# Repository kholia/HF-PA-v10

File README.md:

Why?

We need a QRP PA which does NOT blow up (unlike those 3xBS170 and 4xBS170
designs). We believe that if the FETs blow up (despite best practices and
intentions but under less-than-ideal external conditions), then the design has
FAILED!

[Inspirational Video Link](https://www.youtube.com/watch?v=4r7wHMg5Yjg)

Update (August-2024): https://github.com/kholia/HF-PA-v10/tree/master/IRFP-Hacks-v5-SMD
(or v4 for THT regulator) and SUPSiC GC2M0280120D is all you need for 30W
All-HF PA for 4 USD. For 30W All-HF PA @ 8.5 USD, my tested MOSFET is CREE
C2M0280120D. Use 7815 regulator for powering the UCC gate driver when using the
`*C2M0280120D` MOSFET. SUPSiC GC3M0280090D works very well too and is our top
choice now (as of September, 2024).

Important update (February-2024): LC match for IRF510 @ 28 MHz. 7 turns FT50-6
and 220pF capacitor. Corrected PAE figure is around 50%. 30v @ drain produces
roughly 10W of clean'ish looking RF output. 24v @ drain produces 6W @ 28 MHz.
17v @ drain produces 3.7W.

March-2024 update: LC match for IRF510 @ 50 MHz. T50-6 4 turns and 180pF
capacitor. 24v @ drain produces clean'ish 28.8 Vpp (~2W). PAE is around 25%.
Such is life...

Update (29-September-2023): By removing the gate resistor, we firmly push the
amplifier into more Class-D operation. The MOSFET now remains as cool as a
cucumber!

Update (10-September-2023): The PCB was successfully validated!

Output is 7 to 8 W (before LPF) over a range of 160m to 10m as expected, with a
15V SMPS power supply. With a Pro-BPF attached, the power output is ~5W even at
28 MHz with IRF510! It even puts out 2W @ 50 MHz!

Amplifier characterization (@ 30.7 MHz for some reason, before LPF):

7 volts -> 2W

8 volts -> 3W

9 volts -> 3.5W

10 volts -> 4W

11 volts -> 5W

12 volts -> 6W

14 volts -> 8W

Efficiency is in the range of 45 to 50% which isn't bad ;)

Another result: 17 volts. 14 MHz. NKK LPF. 17.3W DC in. 57.6 clean Vpp on
scope. 8.3W clean RF output @ 48% efficiency!

BOM cost (minimal version): < 450 INR only - beat this! ;)

Note: HF-PA-v10 is also known as `CoolAMP (TM)`.

Build Notes:

- Use a 15V / 16v power supply.

- If you want to use a 13.8V power supply, then

  - Do NOT install the 78M12 regulator

  - Bridge the JP2 jumper

- Use adequate heatsinking. I use a 100x100x200 aluminium block with a 12v fan
  for doing WSPR activities. The MOSFET temperature stays under 45 degrees this
  way.

- PTT is active high - 3.3v is enough to trigger PTT.

- To skip the PTT sub-circuit, bridge the AOD407 MOSFET's source to drain.

- This amplifier can be directly driven by Si5351 (use 8mA drive setting)!

- IMPORTANT: For safety and RF output control, use a `10A DC-DC Step-down
  Adjustable Constant Voltage Module` or something similar.

  - https://robu.in/product/10a-dc-dc-step-down-adjustable-constant-voltage-module/

Results:

Fun on WSPR:

Note: I am using a 5-meter long EFHW antenna tuned for the 10m band along with
~45 meters of HLF-240 coax. Your results should be better than mine ;)

Quick Hacks:

I am using one v10 board (on low power setting of ~1 to 2W) to drive the second
v10 board.

The second v10 board has IRF530 on it. It uses a simple 3R3 SMD drain choke,
240nH inductor (8 turns on T50-6) + 470 pF LC match for the 20m band at the
output side.

The power output is 20W+ with 30v at the IRF530 drain. While this is fine for
FT8, we decrease the output power to 9 to 12W for WSPR mode (considering
derating, heat dissipation, fear of "flash over")

December-2023 update: We can now use IRFP140N (with its massive TO-247 package)
to generate around "20W" safely for WSPR. We drive the IRFP140N MOSFET directly
with the UCC driver chip now.

Settings: UCC driver at roughly 12v. With LC match set for 20m band (NB!).

IRFP140N @ 28v drain @ 14 MHz -> 22W

IRFP140N @ 28v drain @ 3.5 MHz -> 20W (for Rafal)

IRFP140N @ 28v drain @ 7 MHz -> 20W

We believe we can push 25W easily by feeding 14v to 15v to the UCC driver chip.

The "final" IRFP140N MOSFET remains as cool as a cucumber, pretty boring -
right? Where have the "exciting" days of the MOSFETs blowing up in your face
gone? Just kidding!

NB: To overcome antenna losses (~2.0 SWR 20m dipole), lossy 50m meters of
HLF-200 coax, we need to generate around 15W+ on the amplifier side.

```
In [1]: 15W * 0.88 (SWR losses) * 0.40 (coax losses)
Out[1]: 5.28
```

PA protection:

- We plan to use INA219 to monitor current consumption, and to terminate TX if
  anomalies are detected.

- Use `thermocouple` attached to the MOSFET's body using thermoglue to monitor
  the temperature, and to terminate TX if anomalies are detected.

New discoveries (via https://github.com/rafal-rozestwinski):

- Power output is 1 to 1.5W on 50 MHz.

- The PA survives open and short conditions but protections are recommended in
  any case.

  - INA219 based current monitoring

  - Thermocouple based temperature monitoring

- We do NOT recommend the old-skool SWR monitoring approach due to its
  complexity (for end-users).

Learnings:

- Keep the IRF510's gate voltage <=9 volts.

  If the IRF510's gate voltage is too high (i.e. when IRF510 is over-driven),
  it results in super wide-band distorted noisy signal on the output - you
  don't want that ;)

  If you want to feed high voltages to IRF's drain, then use a regulator (9v)
  for powering the UCC driver chip.

Joining In:

Are you interested in such projects, and spam-free technical discussions?

If yes, you might be interested in joining [the 'HAMBREWERS' Telegram group](https://t.me/+TwzGyKGe8_QI_B3y).

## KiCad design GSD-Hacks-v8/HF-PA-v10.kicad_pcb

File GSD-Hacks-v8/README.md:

This version uses a GaN gate driver (MX1025D) and GSD pinout TO-252 package GaN FET. It also uses a cost-effective Chinese `coupled inductor`.

Works without extra cooling at 12V to 15V drain. 20V drain needs extra cooling for heavy duty cycles. 

For WSPR, I recommend running at 7.5V drain with ~1W output.

This is the same as `GSD-Hacks-v7` but with an 10 ohms series resistor added to the TTL input port.

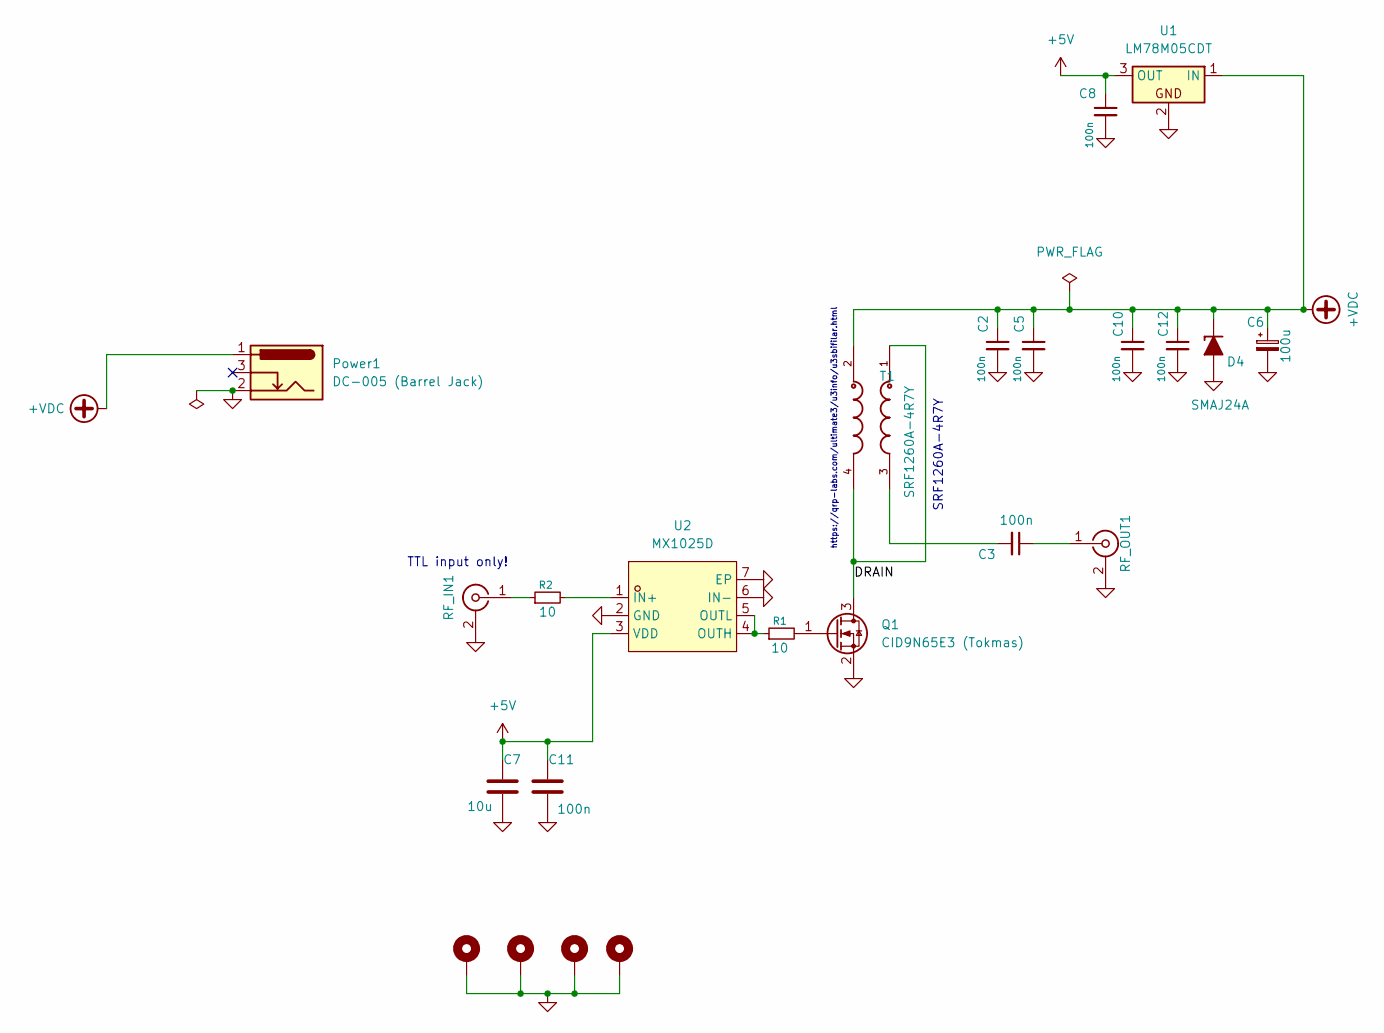
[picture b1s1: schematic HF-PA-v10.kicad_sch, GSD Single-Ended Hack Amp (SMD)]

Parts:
C2, C10: 100n; C_0805_2012Metric; LCSC Part C24783
C3, C8: 100n; C_0805_2012Metric; LCSC Part C110255
C5, C12: 100n; C_0805_2012Metric; LCSC Part C55077
C6: 100u; CP_Elec_8x10.5
C7: 10u; C_0805_2012Metric; LCSC Part C110255
C11: 100n; C_0805_2012Metric; LCSC Part C13585
D4: SMAJ24A; D_SMA
H1, H2, H3, H4: MountingHole_Pad; MountingHole_3.2mm_M3_Pad_Via
Power1: DC-005 (Barrel Jack); XKB_DC-005-5A-2.0_Modded
Q1: CID9N65E3 (Tokmas); TO-252-2_L6.6-W6.1-P4.57-LS9.9-BR-CW
R1, R2: 10; R_0603_1608Metric_Pad0.98x0.95mm_HandSolder
RF_IN1: SMA; SMA_Samtec_SMA-J-P-H-ST-EM1_EdgeMount
RF_OUT1: SMA; SMA_Samtec_SMA-J-P-H-ST-EM1_EdgeMount
T1: SRF1260A-4R7Y; IND_SRF1260A-4R7Y-Longer-Pads; LCSC Part C3273481
U1: LM78M05CDT; TO-252-2-Longer
U2: MX1025D; TDFN-6_L2.0-W2.0-P0.65-BL-EP; LCSC Part C5341121

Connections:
+5V: C7.1, C8.1, C11.1, U1.3 (OUT), U2.3 (VDD)
+VDC: C2.1, C5.1, C6.1, C10.1, C12.1, D4.1 (K), Power1.1, T1.2, U1.1 (IN)
/DRAIN: Q1.3 (D), T1.1, T1.4
GND: C2.2, C5.2, C6.2, C7.2, C8.2, C10.2, C11.2, C12.2, D4.2 (A), H1.1, H2.1, H3.1, H4.1, Power1.2, Q1.2 (S), RF_IN1.2 (Ext), RF_OUT1.2 (Ext), U1.2, U2.2 (GND), U2.6 (IN-), U2.7 (EP)
unnamed: C3.2, T1.3
unnamed: Q1.1 (G), R1.2
unnamed: R2.1, RF_IN1.1 (In)
unnamed: C3.1, RF_OUT1.1 (In)
unnamed: R2.2, U2.1 (IN+)
unnamed: R1.1, U2.4 (OUTH), U2.5 (OUTL)

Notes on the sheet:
https://qrp-labs.com/ultimate3/u3info/u3sbifilar.html
SRF1260A-4R7Y
TTL input only!

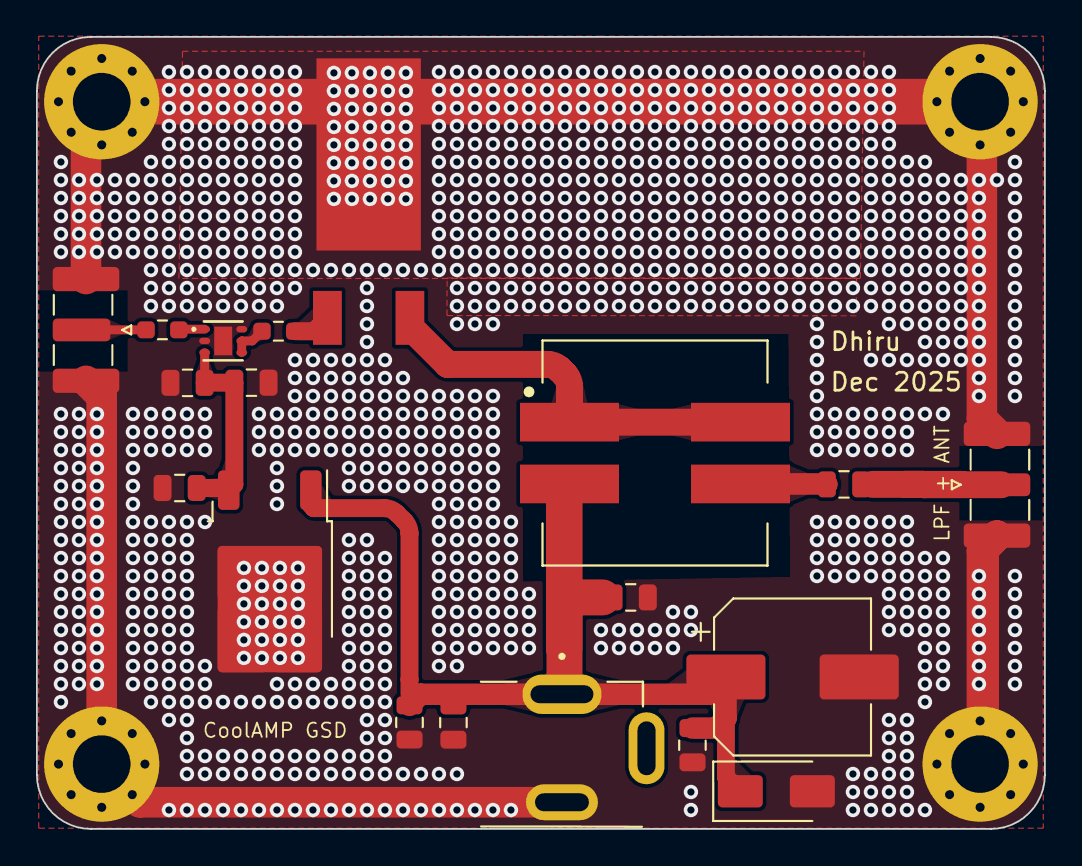
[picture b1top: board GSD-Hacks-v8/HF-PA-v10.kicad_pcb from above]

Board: 2 copper layers, 56.0 x 44.0 mm, 23 parts (0 on the bottom side), 10 nets.

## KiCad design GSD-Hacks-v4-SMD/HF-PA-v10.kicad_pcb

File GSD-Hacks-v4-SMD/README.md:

This version uses SOIC-8 gate driver (NCP81074ADR2G) and GSD pinout TO-252 package FET.

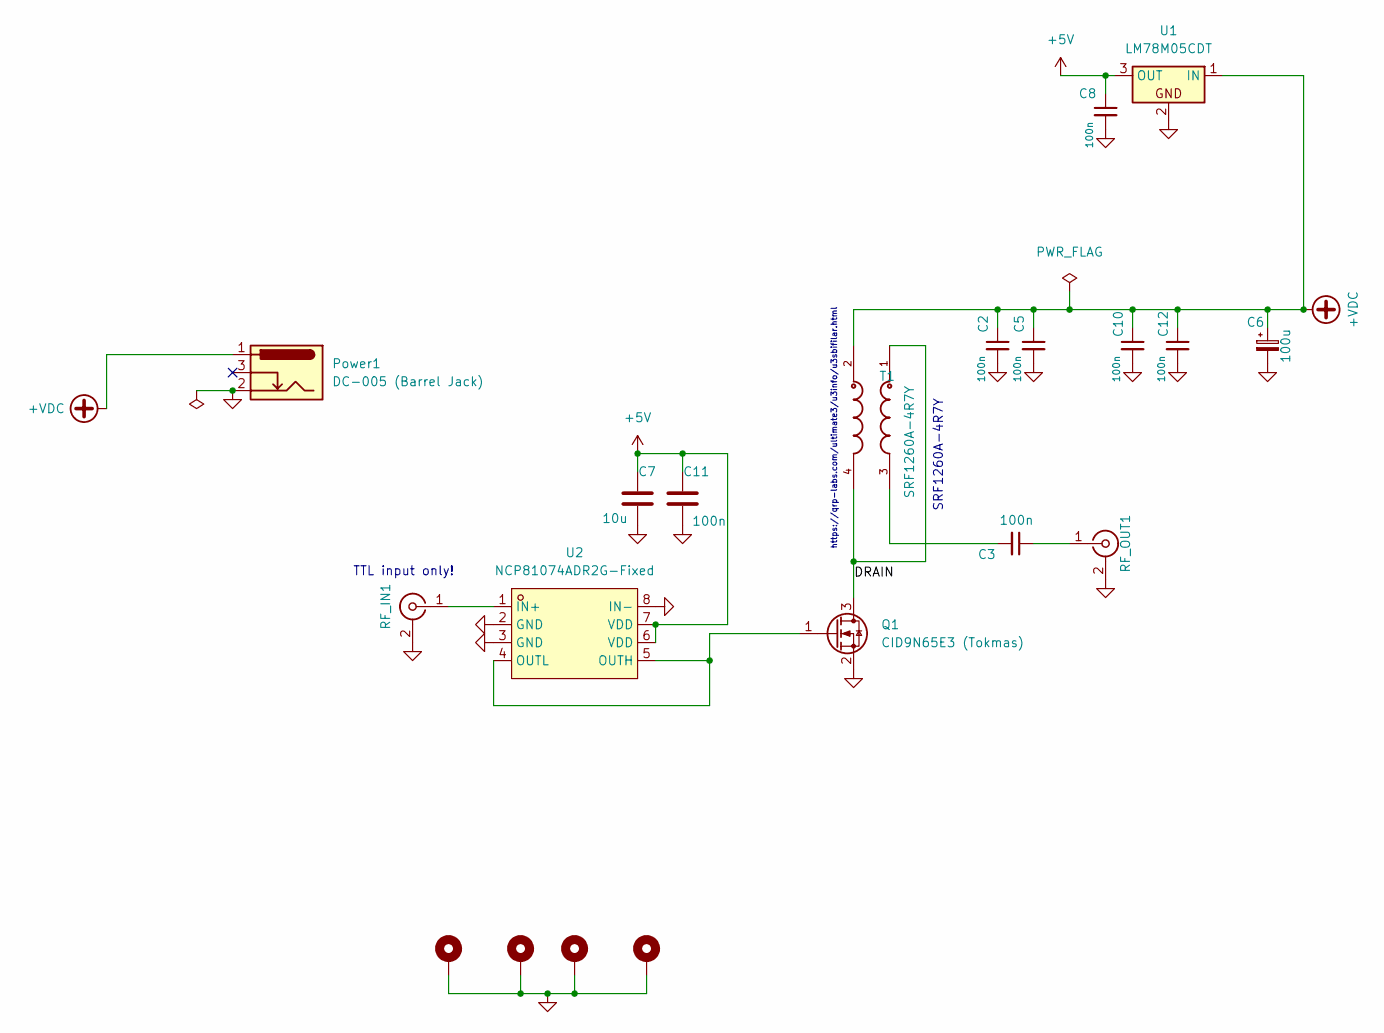
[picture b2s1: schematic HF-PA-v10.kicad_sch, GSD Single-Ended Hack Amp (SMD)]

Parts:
C2, C10: 100n; C_1206_3216Metric_Pad1.33x1.80mm_HandSolder; LCSC Part C24783
C3, C8: 100n; C_1206_3216Metric_Pad1.33x1.80mm_HandSolder; LCSC Part C110255
C5, C12: 100n; C_1206_3216Metric_Pad1.33x1.80mm_HandSolder; LCSC Part C55077
C6: 100u; CP_Radial_D8.0mm_P5.00mm
C7: 10u; C_1206_3216Metric_Pad1.33x1.80mm_HandSolder; LCSC Part C110255
C11: 100n; C_1206_3216Metric_Pad1.33x1.80mm_HandSolder; LCSC Part C13585
H1, H2, H3, H4: MountingHole_Pad; MountingHole_3.2mm_M3_Pad_Via
Power1: DC-005 (Barrel Jack); XKB_DC-005-5A-2.0_Modded
Q1: CID9N65E3 (Tokmas); TO-252-2_L6.6-W6.1-P4.57-LS9.9-BR-CW
RF_IN1: SMA; SMA_Samtec_SMA-J-P-H-ST-EM1_EdgeMount
RF_OUT1: SMA; SMA_Samtec_SMA-J-P-H-ST-EM1_EdgeMount
T1: SRF1260A-4R7Y; IND_SRF1260A-4R7Y-Longer-Pads; LCSC Part C3273481
U1: LM78M05CDT; TO-252-2
U2: NCP81074ADR2G-Fixed; SOIC-8_3.9x4.9mm_P1.27mm; LCSC Part C603800

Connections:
+5V: C7.1, C8.1, C11.1, U1.3 (OUT), U2.6 (VDD), U2.7 (VDD)
+VDC: C2.1, C5.1, C6.1, C10.1, C12.1, Power1.1, T1.2, U1.1 (IN)
/DRAIN: Q1.3 (D), T1.1, T1.4
GND: C2.2, C5.2, C6.2, C7.2, C8.2, C10.2, C11.2, C12.2, H1.1, H2.1, H3.1, H4.1, Power1.2, Q1.2 (S), RF_IN1.2 (Ext), RF_OUT1.2 (Ext), U1.2, U2.2 (GND), U2.3 (GND), U2.8 (IN-)
unnamed: C3.2, T1.3
unnamed: Q1.1 (G), U2.4 (OUTL), U2.5 (OUTH)
unnamed: RF_IN1.1 (In), U2.1 (IN+)
unnamed: C3.1, RF_OUT1.1 (In)

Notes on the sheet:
https://qrp-labs.com/ultimate3/u3info/u3sbifilar.html
SRF1260A-4R7Y
TTL input only!

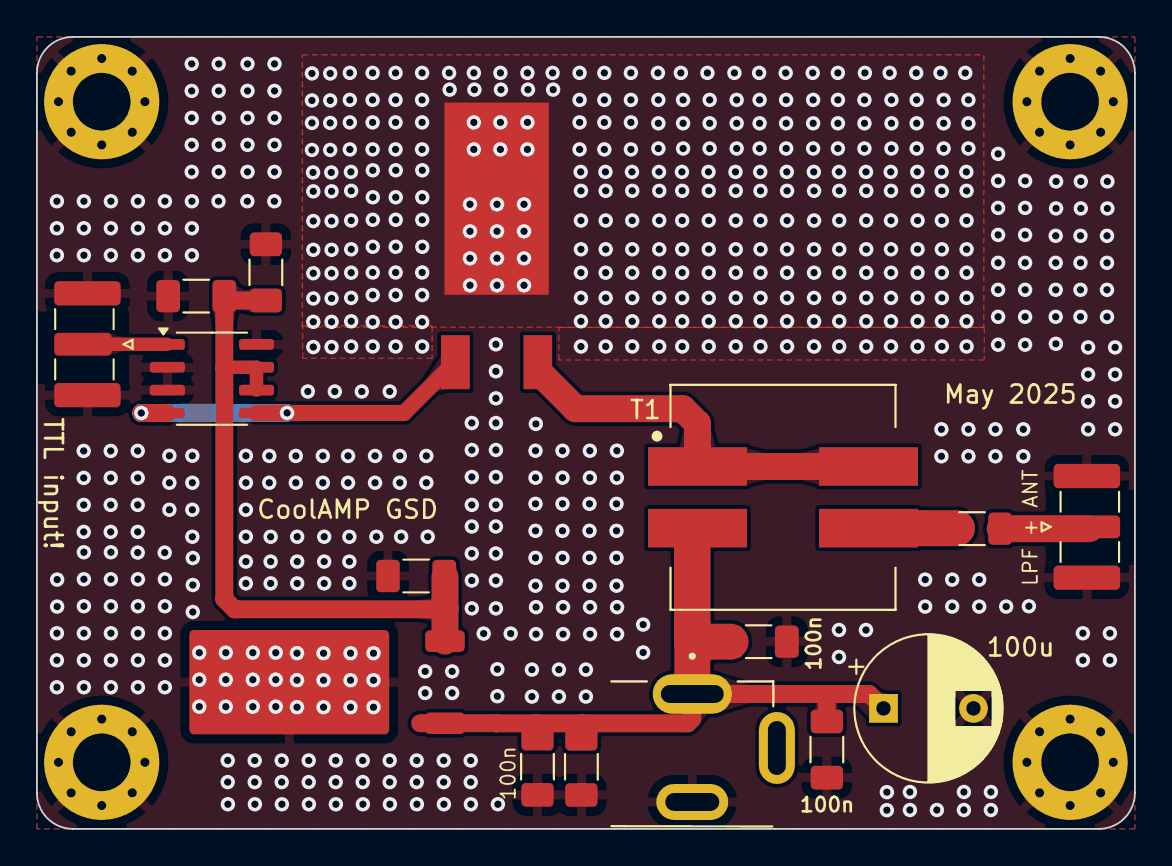
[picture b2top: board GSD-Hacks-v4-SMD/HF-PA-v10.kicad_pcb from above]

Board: 2 copper layers, 61.0 x 44.0 mm, 20 parts (0 on the bottom side), 8 nets.

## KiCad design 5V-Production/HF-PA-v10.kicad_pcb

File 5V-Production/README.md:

This version was created to allow easier experimentation with `VCC = 5v`.

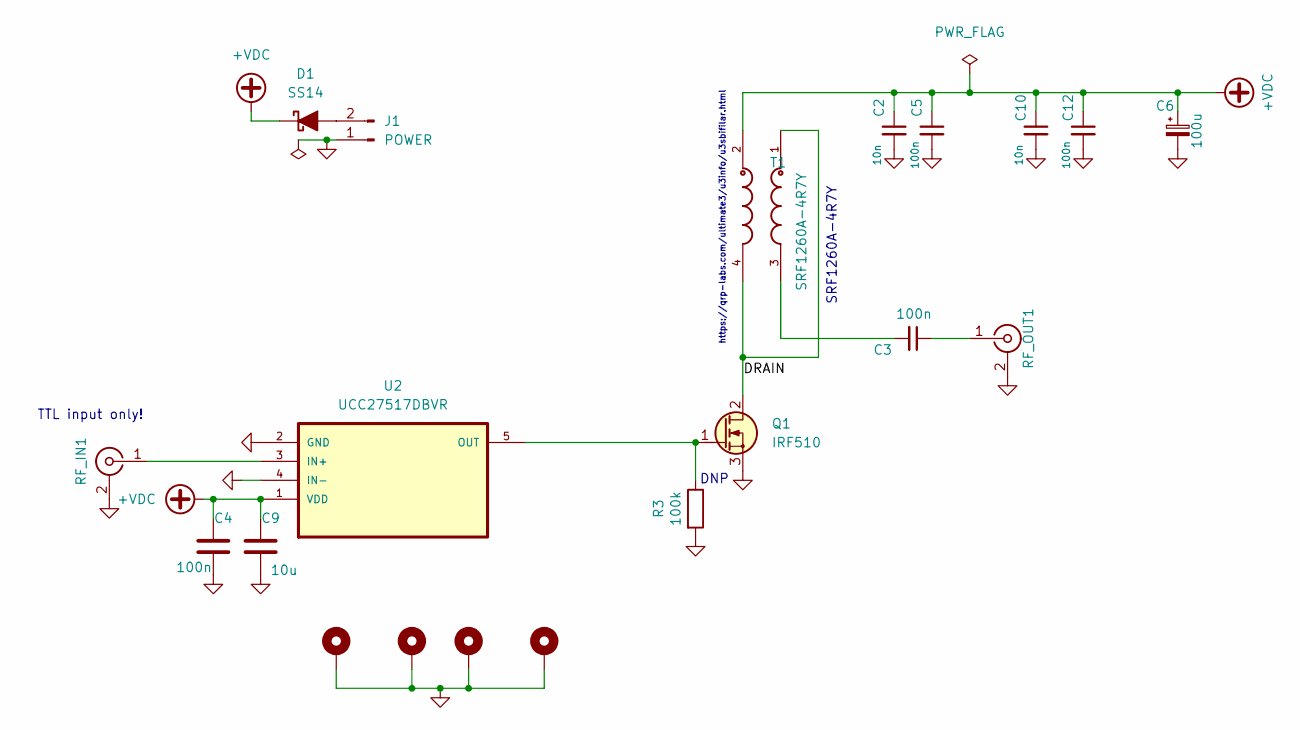
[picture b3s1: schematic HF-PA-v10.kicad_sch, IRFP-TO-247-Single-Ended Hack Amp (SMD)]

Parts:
C2, C10: 10n; C_1206_3216Metric_Pad1.33x1.80mm_HandSolder; LCSC Part C24783
C3, C4: 100n; C_1206_3216Metric_Pad1.33x1.80mm_HandSolder; LCSC Part C110255
C5, C12: 100n; C_1206_3216Metric_Pad1.33x1.80mm_HandSolder; LCSC Part C55077
C6: 100u; CP_Radial_D8.0mm_P3.50mm
C9: 10u; C_1206_3216Metric_Pad1.33x1.80mm_HandSolder; LCSC Part C13585
D1: SS14; D_SMA_Handsoldering
H1, H2, H3, H4: MountingHole_Pad; MountingHole_3.2mm_M3_Pad_Via
J1: POWER; JST_PH_B2B-PH-K_1x02_P2.00mm_Vertical
Q1: IRF510; TO-220-3_Horizontal_TabDown
R3: 100k; R_1206_3216Metric_Pad1.30x1.75mm_HandSolder; LCSC Part C17900
RF_IN1: SMA; SMA_Samtec_SMA-J-P-H-ST-EM1_EdgeMount
RF_OUT1: SMA; SMA_Samtec_SMA-J-P-H-ST-EM1_EdgeMount
T1: SRF1260A-4R7Y; IND_SRF1260A-4R7Y-Longer-Pads; LCSC Part C3273481
U2: UCC27517DBVR; TSOT-23-5_HandSoldering; LCSC Part C99395

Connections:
+VDC: C2.1, C4.1, C5.1, C6.1, C9.1, C10.1, C12.1, D1.1 (K), T1.2, U2.1 (VDD)
/DRAIN: Q1.2 (D), T1.1, T1.4
GND: C2.2, C4.2, C5.2, C6.2, C9.2, C10.2, C12.2, H1.1, H2.1, H3.1, H4.1, J1.1, Q1.3 (S), R3.2, RF_IN1.2 (Ext), RF_OUT1.2 (Ext), U2.2 (GND), U2.4 (IN-)
unnamed: C3.2, T1.3
unnamed: D1.2 (A), J1.2
unnamed: Q1.1 (G), R3.1, U2.5 (OUT)
unnamed: RF_IN1.1 (In), U2.3 (IN+)
unnamed: C3.1, RF_OUT1.1 (In)

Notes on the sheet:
DNP
https://qrp-labs.com/ultimate3/u3info/u3sbifilar.html
SRF1260A-4R7Y
TTL input only!

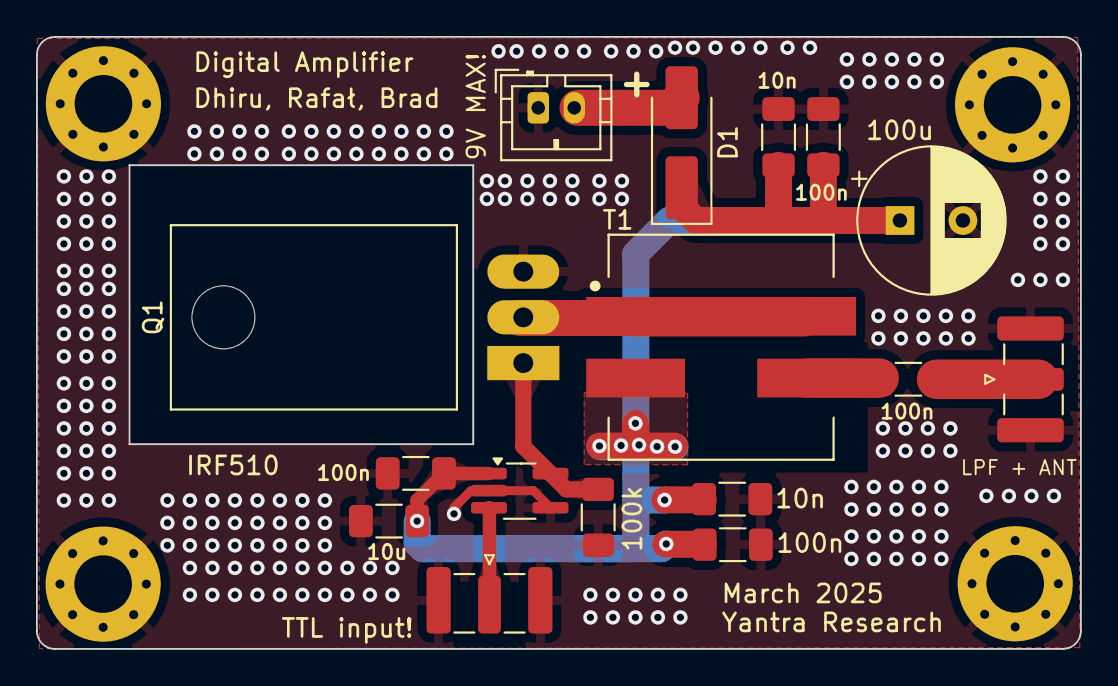
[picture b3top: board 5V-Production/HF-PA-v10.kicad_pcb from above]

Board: 2 copper layers, 58.0 x 34.0 mm, 20 parts (0 on the bottom side), 8 nets.

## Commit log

2024-01-03 Initial version
2025-04-01 SiC QRO Amplifier
2025-08-17 GSD-Hacks-v4-SMD and v5
2025-12-12 GSD-Hacks-v7
2026-03-05 Add GSD-Hacks-v8
